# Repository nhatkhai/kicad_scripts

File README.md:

# Summary
A set of scripts can be use to work with KiCad

* bom_plugins/bom2sch.py: Update eeschema symbol fields from the first
  table found in CSV BOM file. It will make a minimal change on .sch files.
  Allow simple diff tools make sense.

* bom_plugins/bom2csv.py: Transform xml netlist or root .sch file to CSV
  BOM file. It create two tables for un-grouped, and grouped versions.

* eeschema/reset_footprint.py: Reset all the symbol footprint back to
  default value from libraries

* pcbnew/clone.py: Clone multi-channels layout using schematic hierarchy,
  and Cmts.User zones as marker for clone area. [More Info](pcbnew/README.md)

* convertors/modToPretty.py: Convert old mod file into pretty file.
* convertors/pcb_downgrade.py: Down grade .kicad_pcb or .kicad_mod file
  save by 5.x so that it can be open on 4.x or 5.x

# Developer Information

## References
### Digikey
* Digikey API: https://api-portal.digikey.com/product 
* Digikey web search: https://www.digikey.com/products/en?keywords=ANY_VALUES
* Digikey web search: https://www.digikey.com/products/en?part=DIGIKEY_NUMBER
* Mouser web search: https://www.mouser.com/Search/Refine?Keyword=ANY_VAULES

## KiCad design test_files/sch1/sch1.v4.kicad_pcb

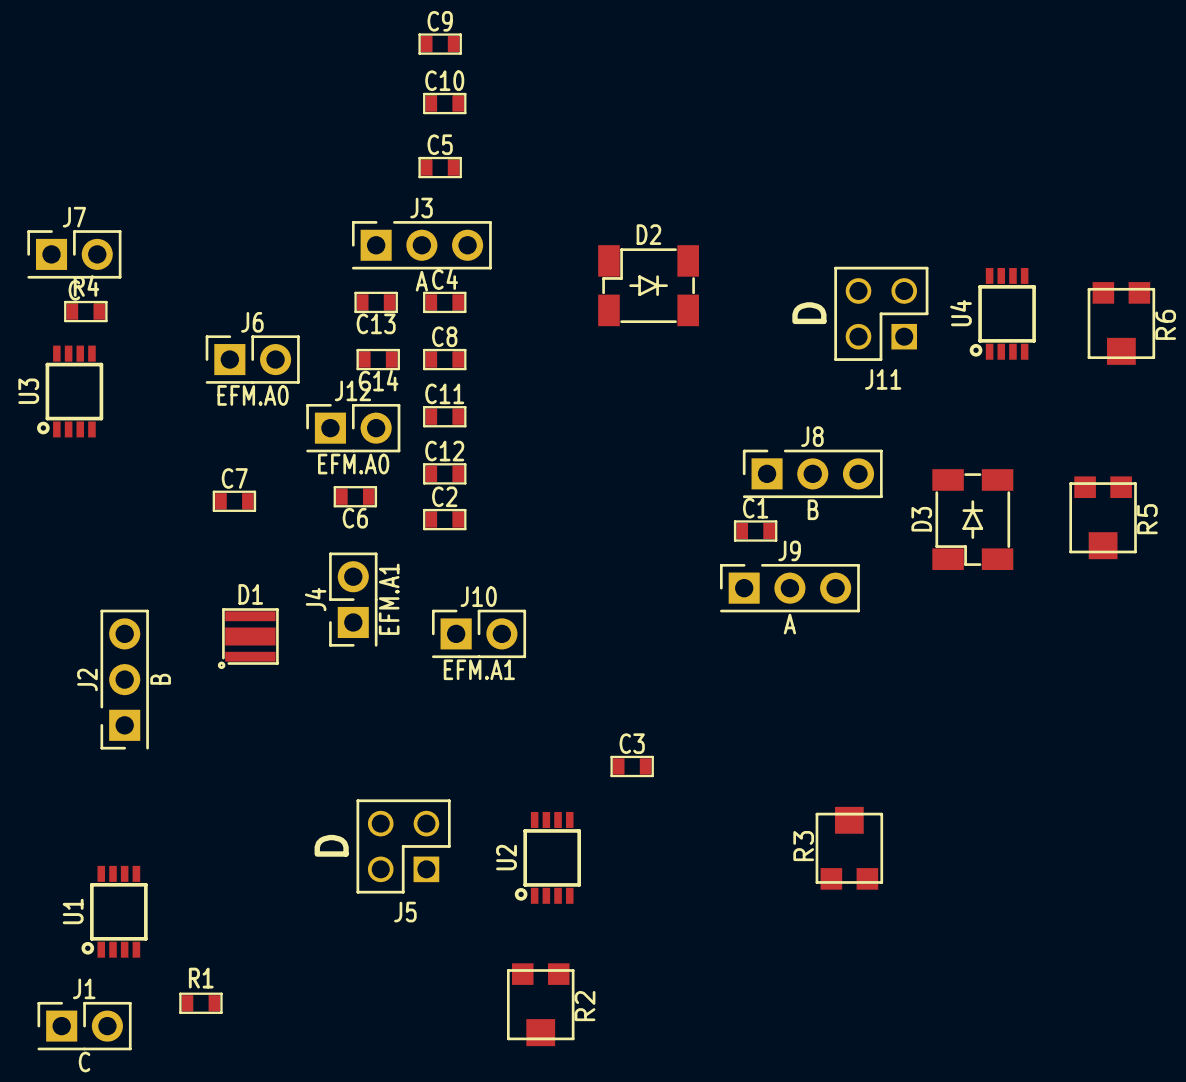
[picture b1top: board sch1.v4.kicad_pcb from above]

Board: 2 copper layers, 39 parts (0 on the bottom side), 22 nets, no tracks yet.

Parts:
C1, C5, C8, C12: 220nF; SM0603_Capacitor
C2, C3, C6, C9, C10, C13: 2.2uF; SM0603_Capacitor
C4, C7, C11, C14: 22uF; SM0603_Capacitor
D1: GH CSSPM1.24; SM1212_ALED_TPAD
D2, D3: TEMD5110X01; 4-SMD_LED
J1, J7: C; Pin_Header_Straight_2x01
J2, J8: B; Pin_Header_Straight_1x03
J3, J9: A; Pin_Header_Straight_1x03
J4, J10: EFM.A1; Pin_Header_Straight_2x01
J5, J11: D; Pin_Header_Straight_2x02
J6, J12: EFM.A0; Pin_Header_Straight_2x01
R1, R4: 4.99kΩ; SM0603_Resistor
R2, R3, R5, R6: 10kΩ; BOURNS_TC33
U1, U2, U3, U4: NCx20072; 8-MSOP

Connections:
+3V3: C6.2, C7.2, C13.2, C14.2, J6.1, J12.1
+5VA: C1.2, C2.2, C3.2, C4.2, C5.2, C8.2, C9.2, C10.2, C11.2, C12.2, D1.1, D2.2, D3.2, J2.1, J4.1, J8.1, J10.1, U1.8, U2.8, U3.8, U4.8
GNDA: C1.1, C2.1, C3.1, C4.1, C5.1, C6.1, C7.1, C8.1, C9.1, C10.1, C11.1, C12.1, C13.1, C14.1, D1.TPAD, J1.2, J3.1, J4.2, J6.2, J7.2, J9.1, J10.2, J12.2, R2.2, R3.2, R5.2, R6.2, U1.4, U1.5, U2.4, U3.4, U3.5, U4.4
unnamed: D1.2, J2.3, J8.3
unnamed: D2.1, J3.3
unnamed: D3.1, J9.3
unnamed: J1.1, R1.1
unnamed: J5.1, U2.1, U2.2
unnamed: J5.3, U2.6, U2.7
unnamed: J7.1, R4.1
unnamed: J11.1, U4.1, U4.2
unnamed: J11.3, U4.6, U4.7
unnamed: R1.2, U1.3
unnamed: R2.3, U2.3
unnamed: R3.1, U2.5
unnamed: R4.2, U3.3
unnamed: R5.3, U4.3
unnamed: R6.1, U4.5
unnamed: U1.1, U1.2
unnamed: U1.6, U1.7
unnamed: U3.1, U3.2
unnamed: U3.6, U3.7

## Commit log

2019-01-23 Add LICENSE
2019-01-23 Initial XML to CSV BOM Script
2019-01-23 Add Bom2sch script
2019-01-23 Add all other 2 years older scripts
2019-01-23 Fix minor issue prompted by pycharm
2019-01-23 Add .gitlab-ci.yml
2019-01-24 Refactor for more features
2019-01-25 Add feature to support Population column use for DNP instead of Value column to reserve original component value
2019-01-26 Correcting import, improve support for Pop/Populate field/column
2019-01-29 Remove POP field in schematic when it empty and same position of value
    * Move bom parser into libs
    * Move custom normPath for either windows or linux into utils
    * Remove POP field from sch file if it empty and same position as value
    * Add delete element info to support deletion of sch field
2019-01-29 Improve groupComponents algorithm from n^2 to n
    * Remove comp.__eq__ which is a bad way of design
    * Improve groupComponents algorithm from n^2 to n
    * Remove getGroupFootprint, getGroupDatasheet which can cause information lost
    * Add more description for bom2csv
2019-01-29 Fix typo, and minor code of sorting list when grouping
2019-01-30 Try to generalize into schCompIter toward multi-file support
    * Fix the fail warn detection for field values joined
    * Make schIter directly take filename, and use in with block
    * Improve and fix relative path detection for windows
    * Add test file - but not yet use for CI
2019-01-31 Add normal test case for bom2sch, and bom2csv
2019-01-31 Correcting __exit__ for multiple iterators
2019-01-31 Update test for debug issue
2019-01-31 Add CONTRIBUTING
2019-02-13 Add support sch file for bom2csv
2019-02-14 Run all the python file as test
2019-02-15 Try kicad docker for test
2019-02-15 Update description for bom2csv and bom2sch
2019-02-17 Add pcb_downgrade script
2019-02-17 Fix the resolution in mm to in convertion for nm precision
2019-03-01 Add readme for pcbnew/clone.py
2019-04-04 line 156 typo txt[11] -> txt[1]
    Fixed a typo that prevented code running.
    Previous error was "IndexError: list index out of range"
    The code now runs to completion
